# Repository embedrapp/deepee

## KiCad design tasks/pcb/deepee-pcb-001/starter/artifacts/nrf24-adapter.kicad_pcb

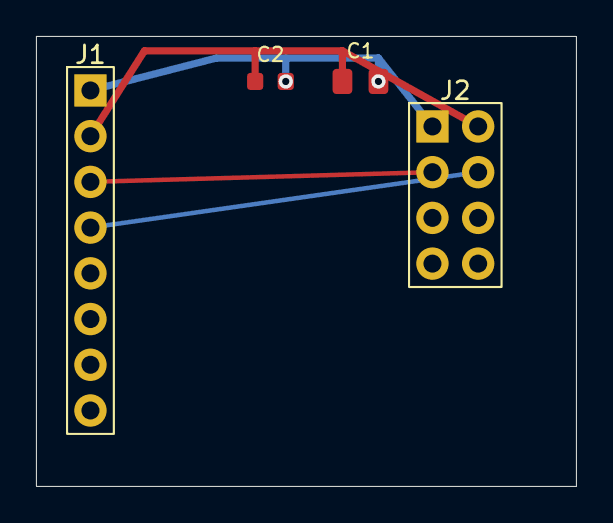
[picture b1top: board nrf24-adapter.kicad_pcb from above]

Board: 2 copper layers, 30.0 x 25.0 mm, 4 parts (0 on the bottom side), 8 nets.

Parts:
C1: 10uF; C_0805_2012Metric
C2: 100nF; C_0603_1608Metric
J1: Conn_01x08; PinHeader_1x08_P2.54mm_Vertical
J2: nRF24L01_Module; PinSocket_2x04_P2.54mm_Vertical

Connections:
+3V3: C1.1, C2.1, J1.2, J2.2
CE: J1.3, J2.3
CSN: J1.4, J2.4
GND: C1.2, C2.2, J1.1, J2.1
IRQ: J1.8, J2.8
MISO: J1.7, J2.7
MOSI: J1.6, J2.6
SCK: J1.5, J2.5

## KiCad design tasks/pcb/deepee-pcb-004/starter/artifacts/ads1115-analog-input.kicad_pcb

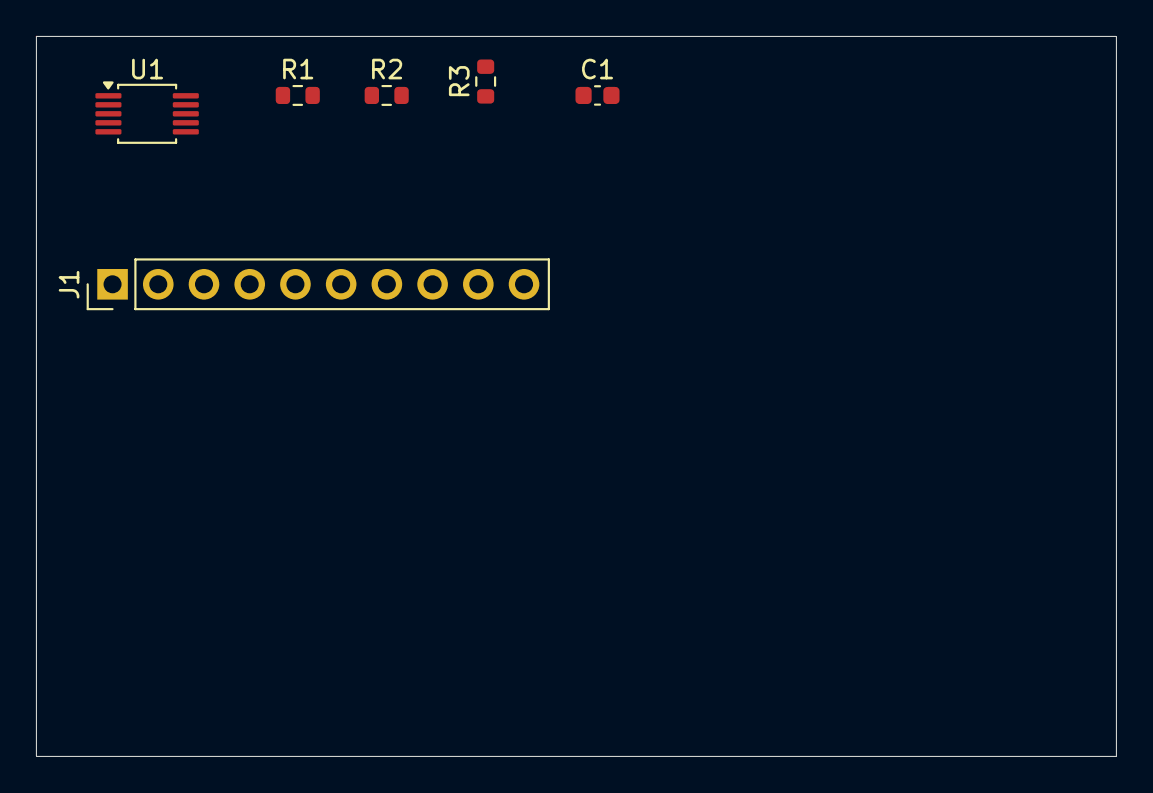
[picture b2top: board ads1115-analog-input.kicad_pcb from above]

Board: 2 copper layers, 60.0 x 40.0 mm, 6 parts (0 on the bottom side), 9 nets, no tracks yet.

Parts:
C1: 100nF; C_0603_1608Metric
J1: Conn_01x10; PinHeader_1x10_P2.54mm_Vertical
R1, R2: 4.7k; R_0603_1608Metric
R3: 10k; R_0603_1608Metric
U1: ADS1115IDGS; TSSOP-10_3x3mm_P0.5mm

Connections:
3V3: C1.1, J1.1, R1.1, R2.1, R3.1, U1.8
AIN0: J1.6, U1.4
AIN1: J1.7, U1.5
AIN2: J1.8, U1.6
AIN3: J1.9, U1.7
ALERT: J1.5, R3.2, U1.2
GND: C1.2, J1.2, J1.10, U1.1, U1.3
SCL: J1.4, R2.2, U1.10
SDA: J1.3, R1.2, U1.9

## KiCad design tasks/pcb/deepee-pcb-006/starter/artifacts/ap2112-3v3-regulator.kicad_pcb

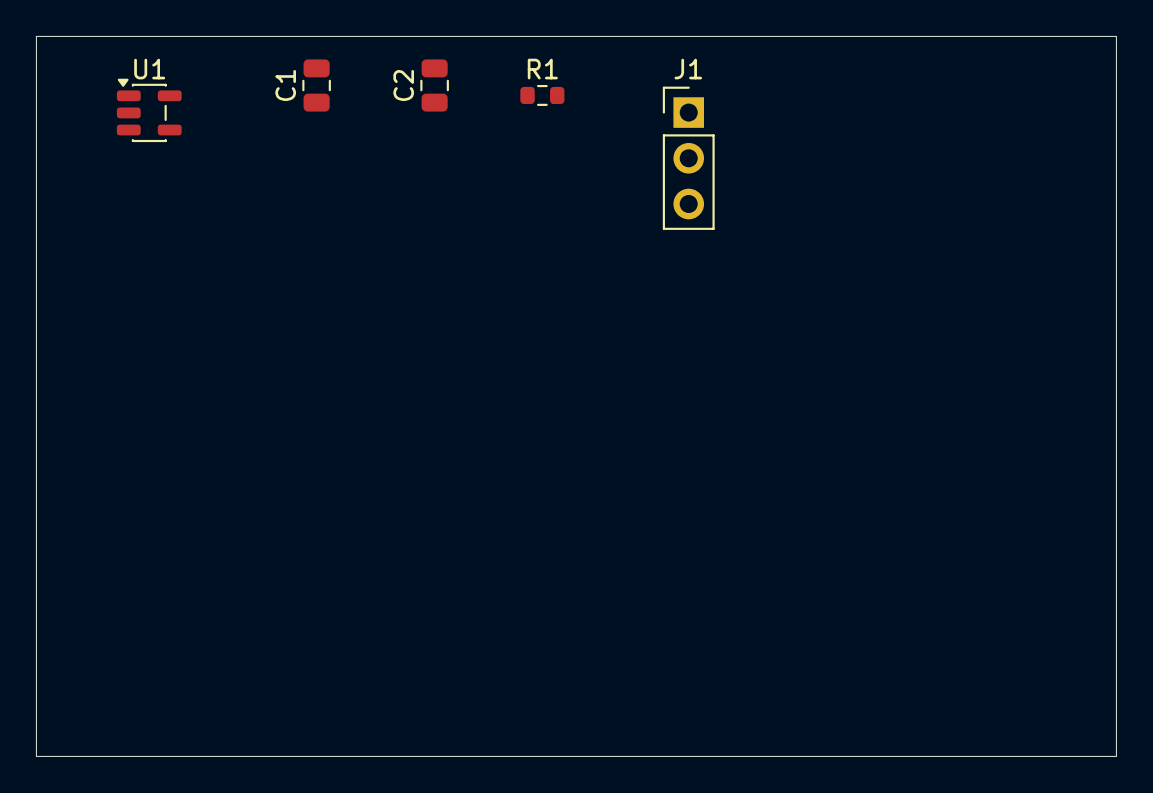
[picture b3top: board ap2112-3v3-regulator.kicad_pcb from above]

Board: 2 copper layers, 60.0 x 40.0 mm, 5 parts (0 on the bottom side), 3 nets, no tracks yet.

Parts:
C1, C2: 1uF; C_0805_2012Metric
J1: Conn_01x03; PinHeader_1x03_P2.54mm_Vertical
R1: 100k; R_0603_1608Metric
U1: AP2112K-3.3; SOT-23-5

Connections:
3V3: C2.1, J1.3, U1.5
GND: C1.2, C2.2, J1.2, R1.2, U1.2
VIN: C1.1, J1.1, R1.1, U1.1, U1.3

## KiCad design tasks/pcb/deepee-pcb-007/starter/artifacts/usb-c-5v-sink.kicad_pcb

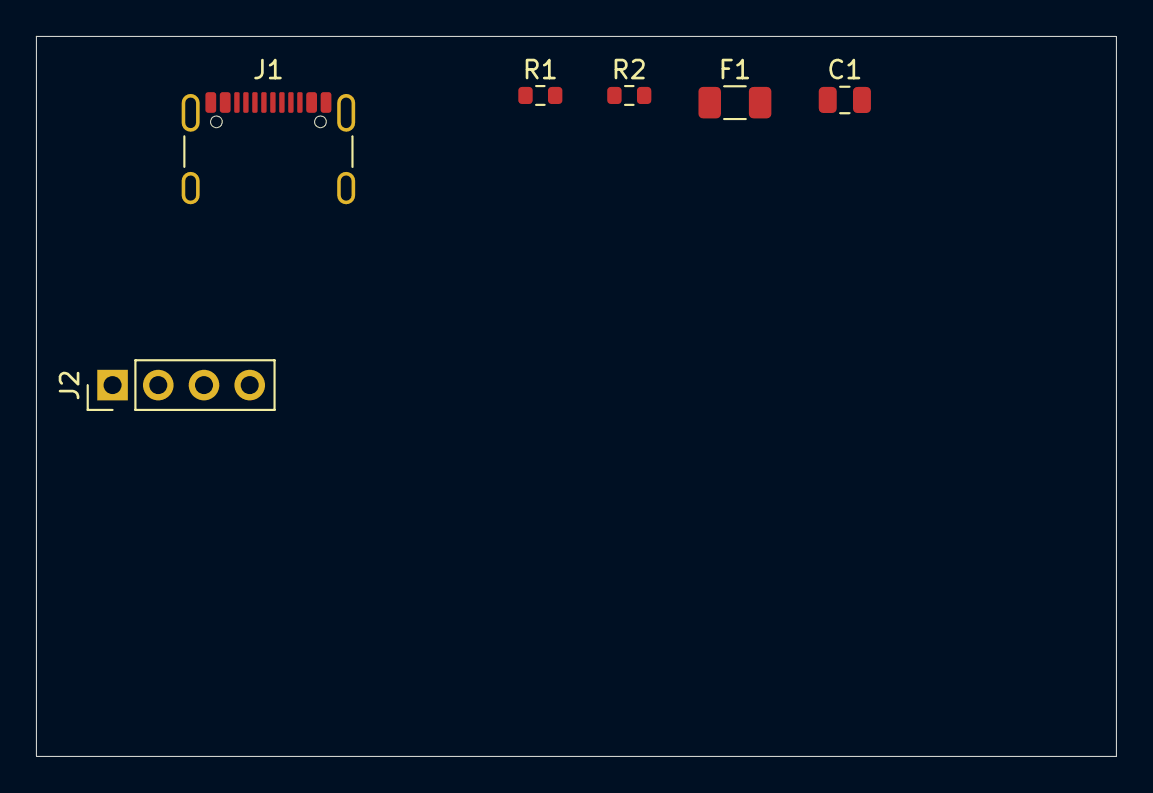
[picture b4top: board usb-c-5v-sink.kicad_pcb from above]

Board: 2 copper layers, 60.0 x 40.0 mm, 6 parts (0 on the bottom side), 7 nets, no tracks yet.

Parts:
C1: 10uF; C_0805_2012Metric
F1: 500mA; Fuse_1206_3216Metric
J1: USB_C_Receptacle_USB2.0_16P; USB_C_Receptacle_GCT_USB4105-xx-A_16P_TopMnt_Horizontal
J2: Conn_01x04; PinHeader_1x04_P2.54mm_Vertical
R1, R2: 5.1k; R_0603_1608Metric

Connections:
5V: C1.1, F1.2, J2.1
CC1: J1.A5, R1.1
CC2: J1.B5, R2.1
GND: C1.2, J1.A1, J1.A12, J1.B1, J1.B12, J1.SH, J2.2, R1.2, R2.2
USB_DM: J1.A7, J1.B7, J2.4
USB_DP: J1.A6, J1.B6, J2.3
VBUS: F1.1, J1.A4, J1.A9, J1.B4, J1.B9

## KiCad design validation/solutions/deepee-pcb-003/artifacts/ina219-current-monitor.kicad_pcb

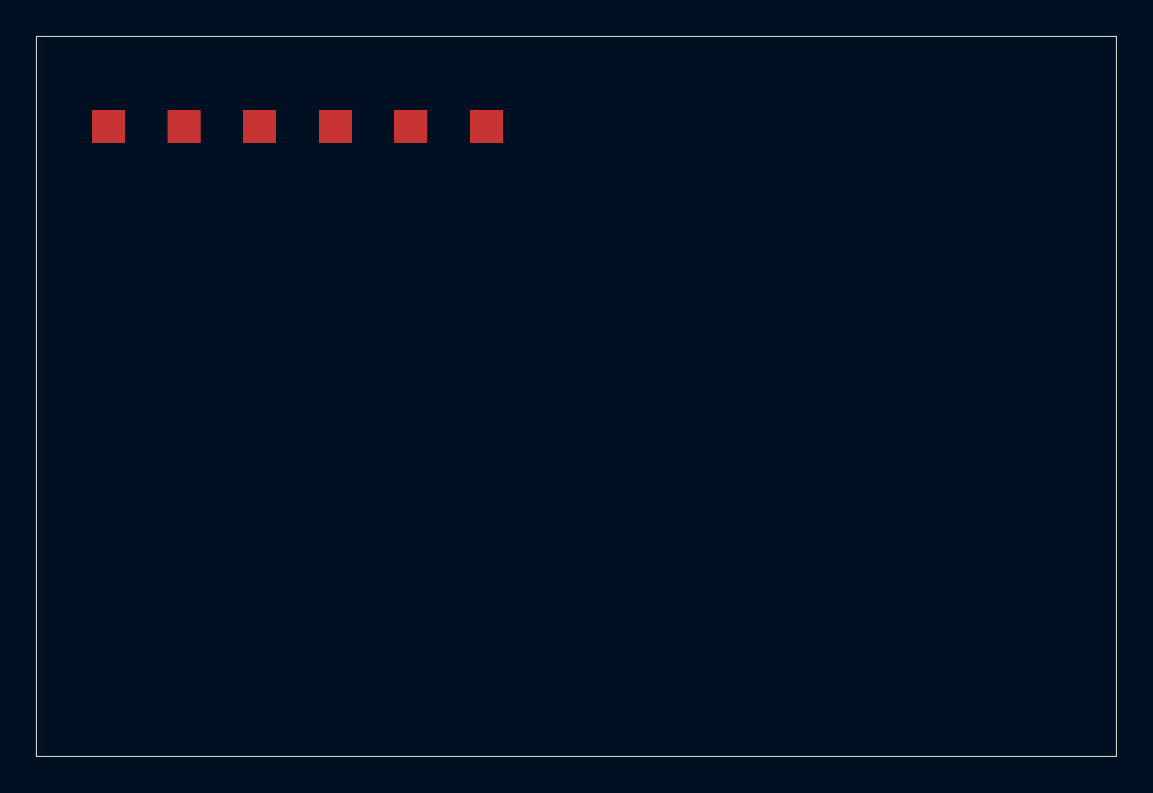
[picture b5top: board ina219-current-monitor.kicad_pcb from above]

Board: 2 copper layers, 60.0 x 40.0 mm, 6 parts (0 on the bottom side), 6 nets.

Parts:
C1: 100nF; C_0603_1608Metric
J1: Conn_01x06; PinHeader_1x06_P2.54mm_Vertical
R1: 0.1R; R_2512_6332Metric
R2, R3: 4.7k; R_0603_1608Metric
U1: INA219AxD; SOIC-8_3.9x4.9mm_P1.27mm

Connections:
3V3: C1.1, J1.3, R2.1, R3.1, U1.5
GND: C1.2, J1.4, U1.1, U1.2, U1.6
SCL: J1.6, R3.2, U1.4
SDA: J1.5, R2.2, U1.3
VIN_IN: J1.1, R1.1, U1.8
VIN_OUT: J1.2, R1.2, U1.7
